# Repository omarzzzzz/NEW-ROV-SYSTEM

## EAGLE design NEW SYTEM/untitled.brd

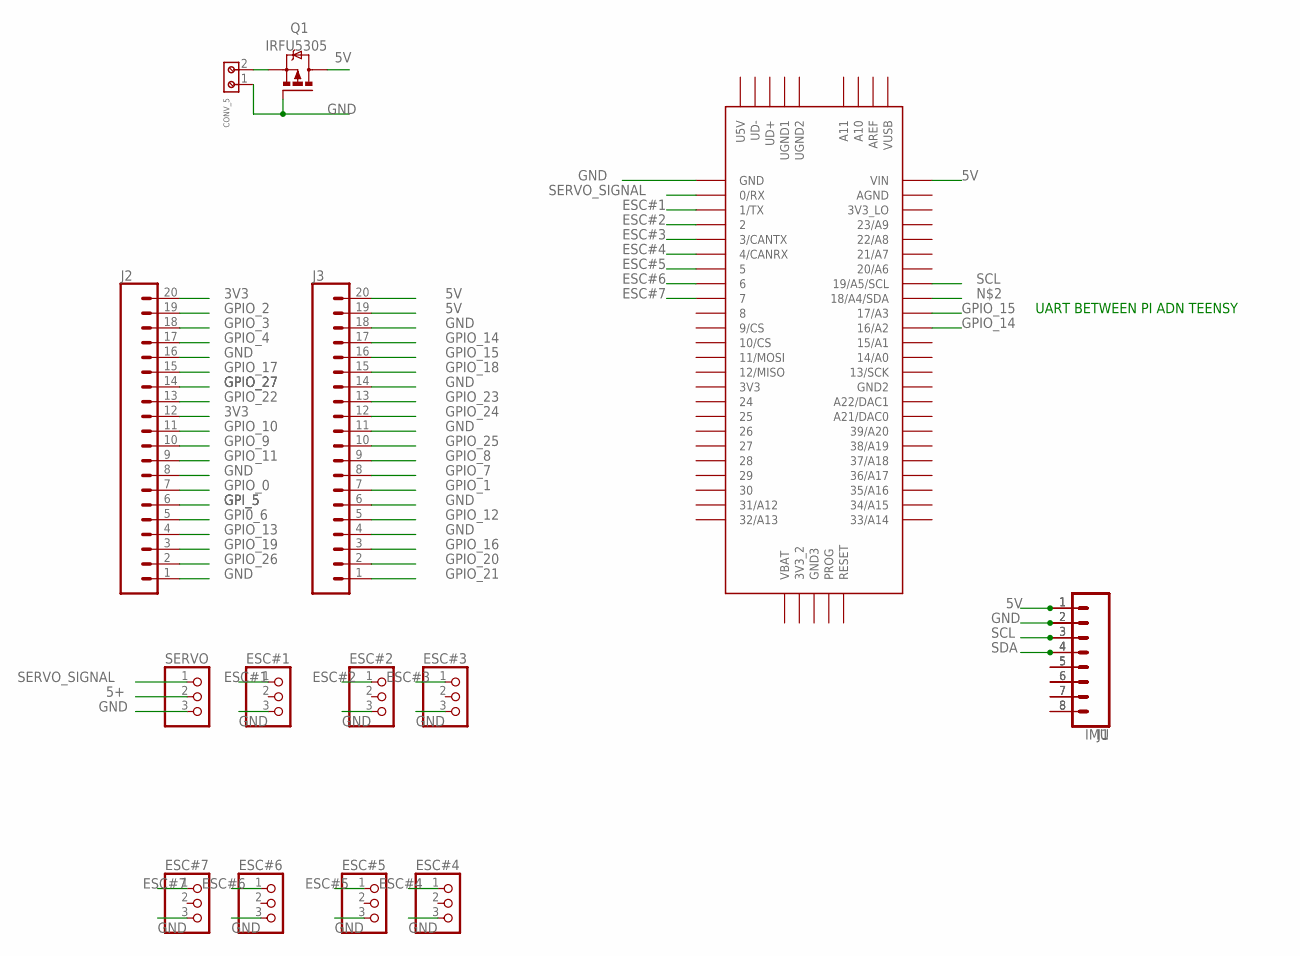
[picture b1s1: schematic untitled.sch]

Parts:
CONV_5: 691213500002
ESC#1, ESC#2, ESC#3, ESC#4, ESC#5, ESC#6, ESC#7: PINHD-1X3; 1X03
IMU: CONN_08"; 1X08
J1: CONN_08"; 1X08
J2, J3: CONN_20; 1X20
Q1: IRFU5305; I-PAK_TO251AA
SERVO: PINHD-1X3; 1X03
U$1: TEENSY_3.5/3.6

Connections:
3V3: J2.12, J2.20
5+: SERVO.2
5V: IMU.1, J1.1, J3.19, J3.20, Q1.2 (D), U$1.VIN
ESC#1: ESC#1.1, U$1.1/TX
ESC#2: ESC#2.1, U$1.2
ESC#3: ESC#3.1, U$1.3/CANTX
ESC#4: ESC#4.1, U$1.4/CANRX
ESC#5: ESC#5.1, U$1.5
ESC#6: ESC#6.1, U$1.6
ESC#7: ESC#7.1, U$1.7
GND: CONV_5.1, ESC#1.3, ESC#2.3, ESC#3.3, ESC#4.3, ESC#5.3, ESC#6.3, ESC#7.3, IMU.2, J1.2, J2.1, J2.8, J2.16, J3.4, J3.6, J3.11, J3.14, J3.18, Q1.1 (G), SERVO.3, U$1.GND
GPI0_6: J2.5
GPIO_0: J2.7
GPIO_1: J3.7
GPIO_2: J2.19
GPIO_3: J2.18
GPIO_4: J2.17
GPIO_7: J3.8
GPIO_8: J3.9
GPIO_9: J2.10
GPIO_10: J2.11
GPIO_11: J2.9
GPIO_12: J3.5
GPIO_13: J2.4
GPIO_14: J3.17, U$1.16/A2
GPIO_15: J3.16, U$1.17/A3
GPIO_16: J3.3
GPIO_17: J2.15
GPIO_18: J3.15
GPIO_19: J2.3
GPIO_20: J3.2
GPIO_21: J3.1
GPIO_22: J2.13
GPIO_23: J3.13
GPIO_24: J3.12
GPIO_25: J3.10
GPIO_26: J2.2
GPIO_27: J2.14
GPI_5: J2.6
unnamed: CONV_5.2, Q1.3 (S)
unnamed: IMU.5, J1.5
unnamed: IMU.6, J1.6
unnamed: IMU.7, J1.7
unnamed: IMU.8, J1.8
SCL: IMU.3, J1.3, U$1.19/A5/SCL
SDA: IMU.4, J1.4
SERVO_SIGNAL: SERVO.1, U$1.0/RX

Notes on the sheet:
UART BETWEEN PI ADN TEENSY

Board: 2 copper layers, 15 parts (0 on the bottom side), 20 nets, no tracks yet.

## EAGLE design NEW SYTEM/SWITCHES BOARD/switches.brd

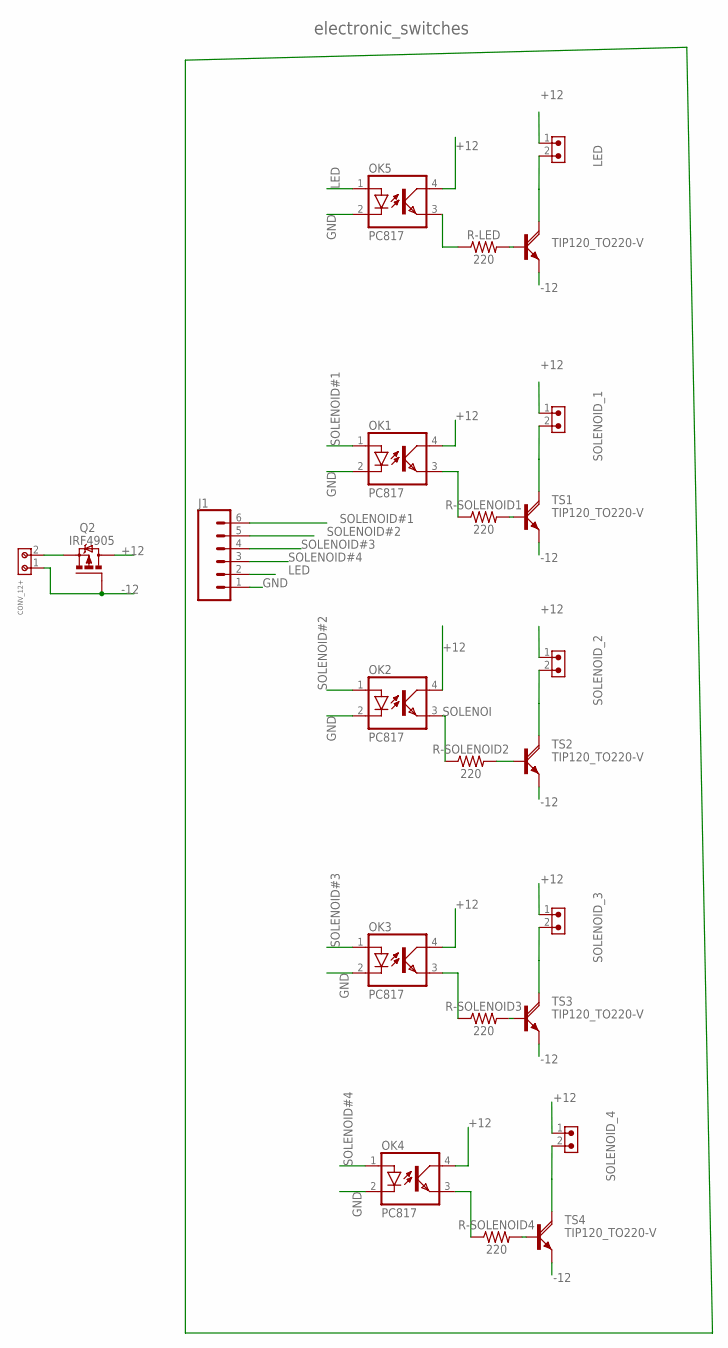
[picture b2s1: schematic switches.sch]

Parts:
CONV_12+: 691213500002
J1: CONN_06FEMALE_LOCK; 1X06_FEMALE_LOCK.010
LED: 691305540002
LED3: TIP120_TO220-V; TO220V
OK1, OK2, OK3, OK4, OK5: PC817; DIL04
Q2: IRF4905; TO220BH
R-LED: 220; AXIAL-0.3
R-SOLENOID1, R-SOLENOID2, R-SOLENOID3, R-SOLENOID4: 220; AXIAL-0.3
SOLENOID_1, SOLENOID_2, SOLENOID_3, SOLENOID_4: 691305540002
TS1, TS2, TS3, TS4: TIP120_TO220-V; TO220V

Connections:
+12: LED.1, OK1.4 (COL), OK2.4 (COL), OK3.4 (COL), OK4.4 (COL), OK5.4 (COL), Q2.D, SOLENOID_1.1, SOLENOID_2.1, SOLENOID_3.1, SOLENOID_4.1
-12: CONV_12+.1, LED3.3 (E), Q2.G, TS1.3 (E), TS2.3 (E), TS3.3 (E), TS4.3 (E)
GND: J1.1, OK1.2 (C), OK2.2 (C), OK3.2 (C), OK4.2 (C), OK5.2 (C)
L1: OK3.3 (EMIT), R-SOLENOID3.P$1 (1)
L2: OK4.3 (EMIT), R-SOLENOID4.P$1 (1)
LED: J1.2, OK5.1 (A)
unnamed: SOLENOID_4.2, TS4.2 (C)
unnamed: R-SOLENOID4.P$2 (2), TS4.1 (B)
unnamed: CONV_12+.2, Q2.S
unnamed: LED.2, LED3.2 (C)
unnamed: LED3.1 (B), R-LED.P$2 (2)
unnamed: SOLENOID_1.2, TS1.2 (C)
unnamed: R-SOLENOID1.P$2 (2), TS1.1 (B)
unnamed: SOLENOID_2.2, TS2.2 (C)
unnamed: R-SOLENOID2.P$2 (2), TS2.1 (B)
unnamed: SOLENOID_3.2, TS3.2 (C)
unnamed: R-SOLENOID3.P$2 (2), TS3.1 (B)
unnamed: OK1.3 (EMIT), R-SOLENOID1.P$1 (1)
unnamed: OK5.3 (EMIT), R-LED.P$1 (1)
SOLENOI: OK2.3 (EMIT), R-SOLENOID2.P$1 (1)
SOLENOID#1: J1.6, OK1.1 (A)
SOLENOID#2: J1.5, OK2.1 (A)
SOLENOID#3: J1.4, OK3.1 (A)
SOLENOID#4: J1.3, OK4.1 (A)

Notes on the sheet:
electronic_switches

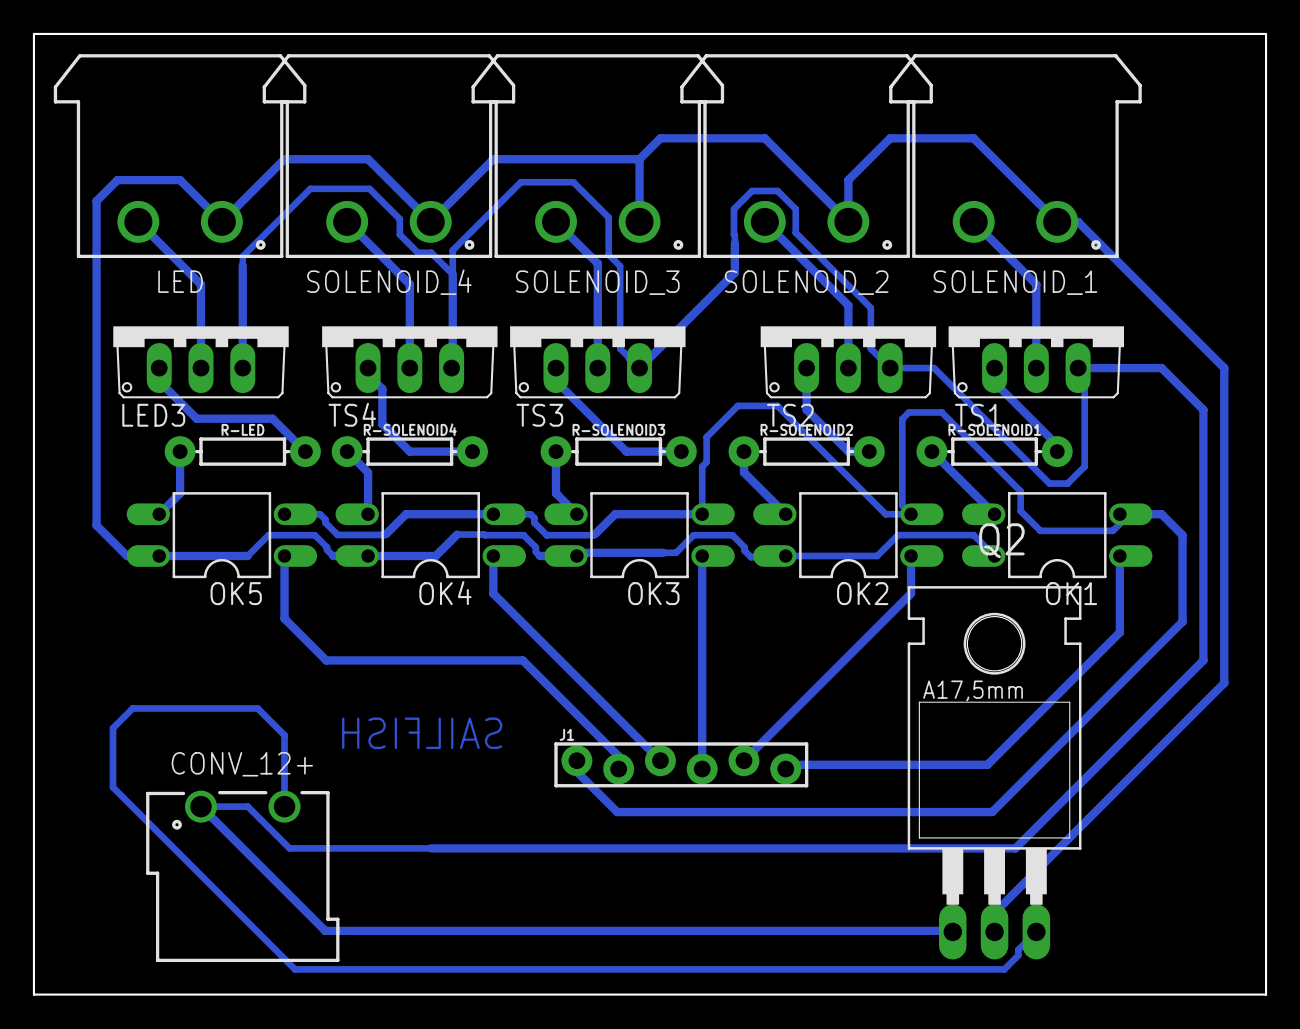
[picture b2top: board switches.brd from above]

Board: 2 copper layers, 74.9 x 58.4 mm, 23 parts (0 on the bottom side), 24 nets.

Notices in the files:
parts and their libraries:
Wurth_Connectors_WR-TBL Rising Cage Clam: Copyright: Würth Elektronik
SparkFun-Resistors: Licensing: Creative Commons ShareAlike 4.0 International - https://creativecommons.org/licenses/by-sa/4.0
